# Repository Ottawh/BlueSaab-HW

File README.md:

# BlueSaab-HW
BlueSaab hardware

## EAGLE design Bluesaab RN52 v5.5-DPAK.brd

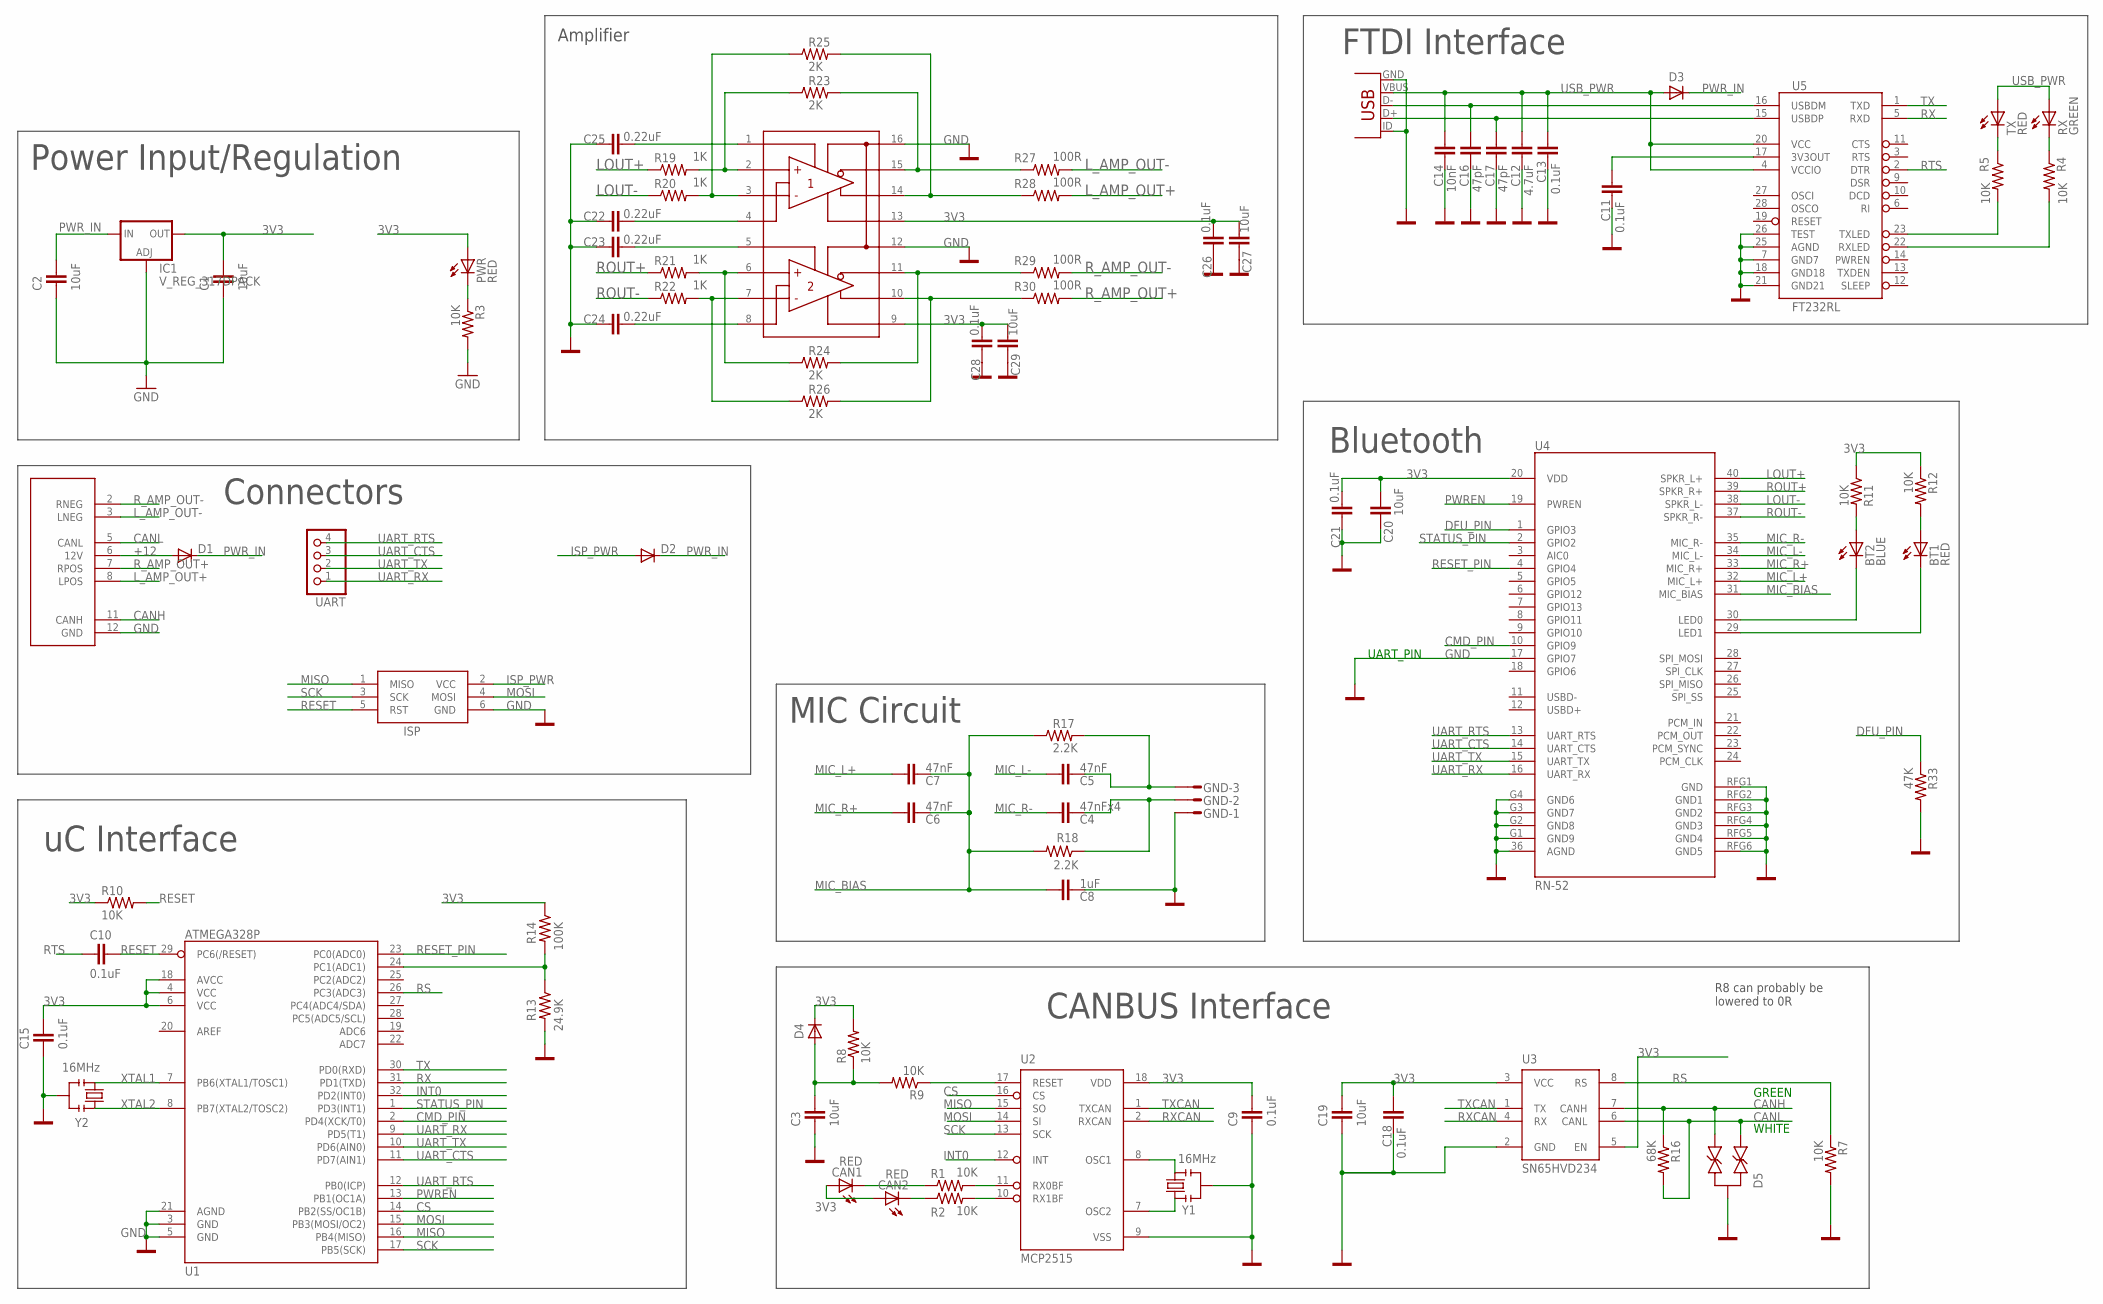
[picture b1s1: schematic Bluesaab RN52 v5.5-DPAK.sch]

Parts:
BT1: RED; CHIPLED_0805
BT2: BLUE; CHIPLED_0805
C1, C2, C3, C19, C20, C27, C29: 10uF; C0805K
C4: 47nFx4; C0805K
C5, C6, C7: 47nF; C0805K
C8: 1uF; C0805K
C9, C10, C11, C13, C15, C18, C21, C26, C28: 0.1uF; C0805K
C12: 4.7uF; C0805K
C14: 10nF; C0805K
C16, C17: 47pF; C0805K
C22, C23, C24, C25: 0.22uF; C0805K
CAN1, CAN2: RED; CHIPLED_0805
CDC_CONNECTOR: 827229-1
D1, D2, D3, D4: DIODE-SCHOTTKY_; SOD123
D5: DIODE-ARRAY; SOT23
GND: S03P
IC1: V_REG_317DPACK; V-REG_DPACK
ISP: AVRISP-6; AVRISP
PWR: RED; CHIPLED_0805
R1, R2, R3, R4, R5, R7, R8, R9, R10, R11, R12: 10K; R0805
R13: 24.9K; R0805
R14: 100K; R0805
R16: 68K; R0805
R17, R18: 2.2K; R0805
R19, R20, R21, R22: 1K; R0805
R23, R24, R25, R26: 2K; R0805
R27, R28, R29, R30: 100R; R0805
R33: 47K; R0805
RX: GREEN; CHIPLED_0805
TX: RED; CHIPLED_0805
U1: ATMEGA328P; TQFP32-08
U2: MCP2515; SO18L
U3: SN65HVD234; SO8
U4: RN-52
U5: FT232RL; SSOP28DB
U7: THS4522; TSSOP-16
UART: PINHD-1X4; 1X04
UPLOAD: USB-MB-H
Y1, Y2: 16MHz; RESONATOR-SMD

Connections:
3V3: C1.2, C9.2, C15.2, C18.1, C19.2, C20.1, C21.2, C26.2, C27.1, C28.2, C29.1, CAN1.A, CAN2.A, D4.C, IC1.4 (OUT), PWR.A, R8.2, R10.1, R11.1, R12.1, R14.1, U1.4 (VCC), U1.6 (VCC), U1.18 (AVCC), U2.18 (VDD), U3.3 (VCC), U3.5 (EN), U4.20 (VDD), U7.9 (9.VS+2), U7.13 (13.VS+1)
3V3OUT: C11.1, U5.17 (3V3OUT)
+12: CDC_CONNECTOR.6 (12V), D1.A
CANH: CDC_CONNECTOR.11 (CANH), D5.2, R16.1, U3.7 (CANH)
CANL: CDC_CONNECTOR.5 (CANL), D5.1, R16.2, U3.6 (CANL)
CMD_PIN: U1.2 (PD4(XCK/T0)), U4.10 (GPIO9)
CS: U1.14 (PB2(SS/OC1B)), U2.16 (CS)
DFU_PIN: R33.1, U4.1 (GPIO3)
GND: C1.1, C2.1, C3.1, C8.1, C9.1, C11.2, C12.1, C13.2, C14.1, C15.1, C16.1, C17.1, C18.2, C19.1, C20.2, C21.1, C22.2, C23.2, C24.2, C25.2, C26.1, C27.2, C28.1, C29.2, CDC_CONNECTOR.12 (GND), D5.3, GND.1, IC1.1 (ADJ), ISP.6 (GND), R3.2, R7.2, R13.2, R33.2, U1.3 (GND), U1.5 (GND), U1.21 (AGND), U2.9 (VSS), U3.2 (GND), U4.17 (GPIO7), U4.36 (AGND), U4.G1 (GND9), U4.G2 (GND8), U4.G3 (GND7), U4.G4 (GND6), U4.RFG1 (GND), U4.RFG2 (GND1), U4.RFG3 (GND2), U4.RFG4 (GND3), U4.RFG5 (GND4), U4.RFG6 (GND5), U5.7 (GND7), U5.18 (GND18), U5.21 (GND21), U5.25 (AGND), U5.26 (TEST), U7.12 (12.VS-), U7.16 (16.VS-), UPLOAD.GND, UPLOAD.ID, Y1.2, Y2.2
INT0: U1.32 (PD2(INT0)), U2.12 (INT)
ISP_PWR: D2.A, ISP.2 (VCC)
LOUT+: R19.1, U4.40 (SPKR_L+)
LOUT-: R20.1, U4.38 (SPKR_L-)
L_AMP_OUT+: CDC_CONNECTOR.8 (LPOS), R28.2
L_AMP_OUT-: CDC_CONNECTOR.3 (LNEG), R27.2
MIC_BIAS: C6.1, C7.1, C8.2, R17.1, R18.2, U4.31 (MIC_BIAS)
MIC_L+: C7.2, U4.32 (MIC_L+)
MIC_L-: C5.1, U4.34 (MIC_L-)
MIC_R+: C6.2, U4.33 (MIC_R+)
MIC_R-: C4.1, U4.35 (MIC_R-)
MISO: ISP.1 (MISO), U1.16 (PB4(MISO)), U2.15 (SO)
MOSI: ISP.4 (MOSI), U1.15 (PB3(MOSI/OC2)), U2.14 (SI)
unnamed: R4.2, U5.22 (RXLED)
unnamed: R19.2, R23.1, U7.2 (2.VIN1+)
unnamed: U2.8 (OSC1), Y1.3
unnamed: U2.7 (OSC2), Y1.1
unnamed: BT1.A, R12.2
unnamed: BT2.A, R11.2
unnamed: R9.1, U2.17 (RESET)
unnamed: R13.1, R14.2, U1.24 (PC1(ADC1))
unnamed: R5.2, U5.23 (TXLED)
unnamed: R20.2, R25.1, U7.3 (3.VIN1-)
unnamed: R4.1, RX.C
unnamed: CAN1.C, R1.1
unnamed: R21.2, R24.1, U7.6 (6.IN2+)
unnamed: R5.1, TX.C
unnamed: CAN2.C, R2.1
unnamed: PWR.C, R3.1
unnamed: R1.2, U2.11 (RX0BF)
unnamed: R22.2, R26.1, U7.7 (7.IN2-)
unnamed: C25.1, U7.1 (1.PD1)
unnamed: C23.1, U7.5 (5.PD2)
unnamed: C22.1, U7.4 (4.OCM1)
unnamed: C4.2, GND.2, R18.1
unnamed: R23.2, R27.1, U7.15 (15.VOUT1-)
unnamed: C5.2, GND.3, R17.2
unnamed: R25.2, R28.1, U7.14 (14.VOUT1+)
unnamed: C24.1, U7.8 (8.VOCM2)
unnamed: BT1.C, U4.29 (LED1)
unnamed: BT2.C, U4.30 (LED0)
unnamed: R2.2, U2.10 (RX1BF)
unnamed: R24.2, R29.1, U7.11 (11.VOUT2-)
unnamed: R26.2, R30.1, U7.10 (10.VOUT2+)
unnamed: C3.2, D4.A, R8.1, R9.2
PWREN: U1.13 (PB1(OC1A)), U4.19 (PWREN)
PWR_IN: C2.2, D1.C, D2.C, D3.C, IC1.3 (IN)
RESET: C10.2, ISP.5 (RST), R10.2, U1.29 (PC6(/RESET))
RESET_PIN: U1.23 (PC0(ADC0)), U4.4 (GPIO4)
ROUT+: R21.1, U4.39 (SPKR_R+)
ROUT-: R22.1, U4.37 (SPKR_R-)
RS: R7.1, U1.26 (PC3(ADC3)), U3.8 (RS)
RTS: C10.1, U5.2 (DTR)
RX: U1.31 (PD1(TXD)), U5.5 (RXD)
RXCAN: U2.2 (RXCAN), U3.4 (RX)
R_AMP_OUT+: CDC_CONNECTOR.7 (RPOS), R30.2
R_AMP_OUT-: CDC_CONNECTOR.2 (RNEG), R29.2
SCK: ISP.3 (SCK), U1.17 (PB5(SCK)), U2.13 (SCK)
STATUS_PIN: U1.1 (PD3(INT1)), U4.2 (GPIO2)
TX: U1.30 (PD0(RXD)), U5.1 (TXD)
TXCAN: U2.1 (TXCAN), U3.1 (TX)
UART_CTS: U1.11 (PD7(AIN1)), U4.14 (UART_CTS), UART.3
UART_RTS: U1.12 (PB0(ICP)), U4.13 (UART_RTS), UART.4
UART_RX: U1.9 (PD5(T1)), U4.16 (UART_RX), UART.1
UART_TX: U1.10 (PD6(AIN0)), U4.15 (UART_TX), UART.2
USBDM: C16.2, U5.16 (USBDM), UPLOAD.D-
USBDP: C17.2, U5.15 (USBDP), UPLOAD.D+
USB_PWR: C12.2, C13.1, C14.2, D3.A, RX.A, TX.A, U5.4 (VCCIO), U5.20 (VCC), UPLOAD.VBUS
XTAL1: U1.7 (PB6(XTAL1/TOSC1)), Y2.1
XTAL2: U1.8 (PB7(XTAL2/TOSC2)), Y2.3

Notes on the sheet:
GREEN
WHITE
CANBUS Interface
Connectors
Power Input/Regulation
Bluetooth
MIC Circuit
uC Interface
UART_PIN
FTDI Interface
R8 can probably be lowered to 0R
Amplifier

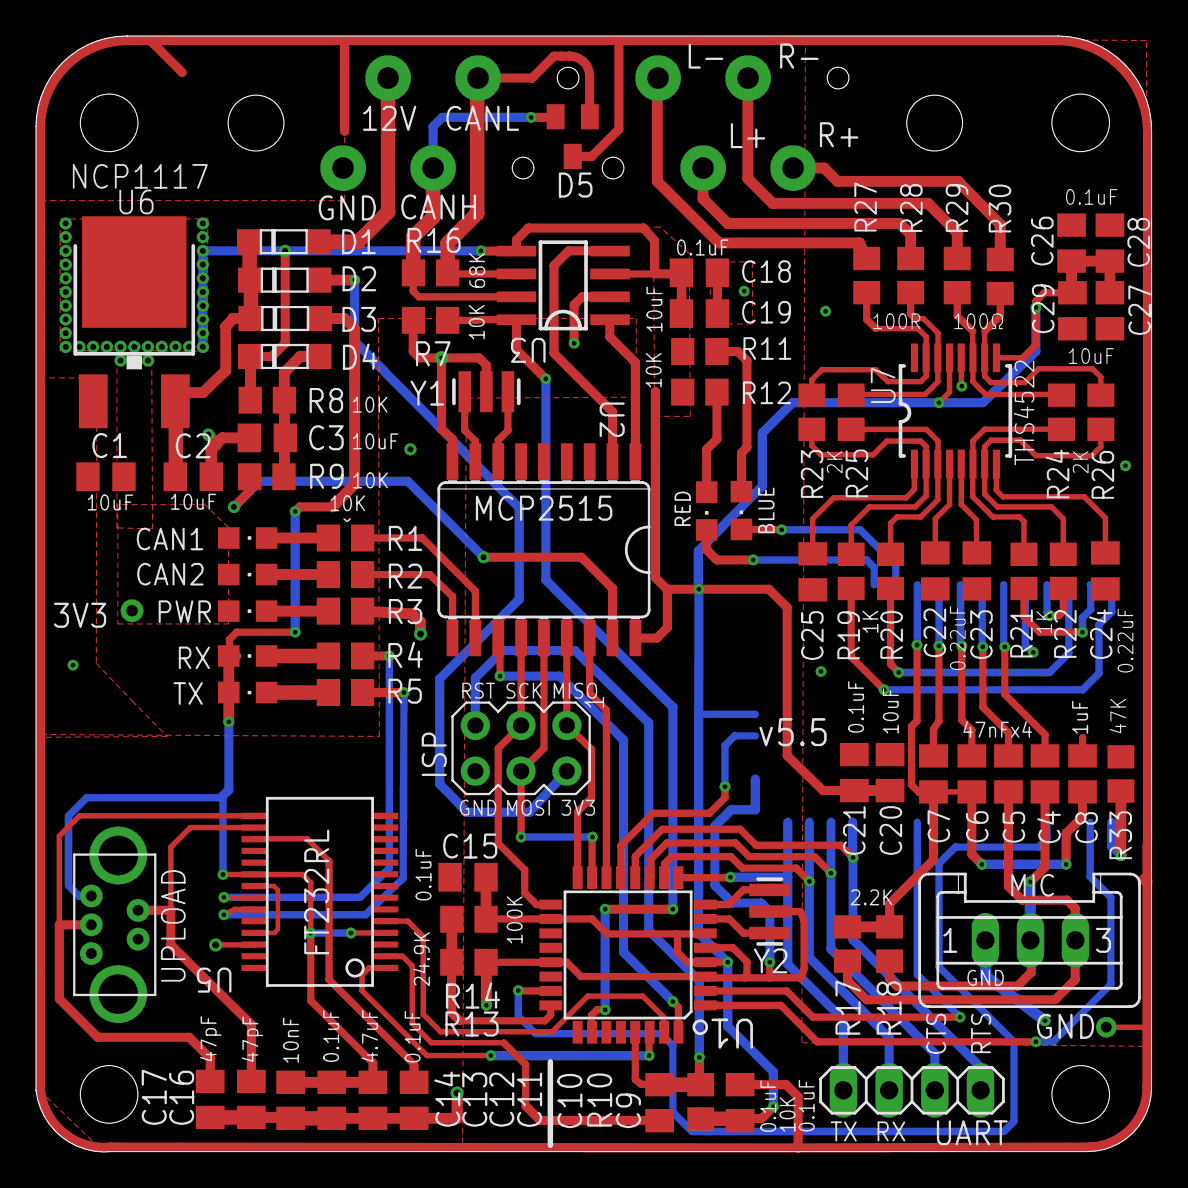
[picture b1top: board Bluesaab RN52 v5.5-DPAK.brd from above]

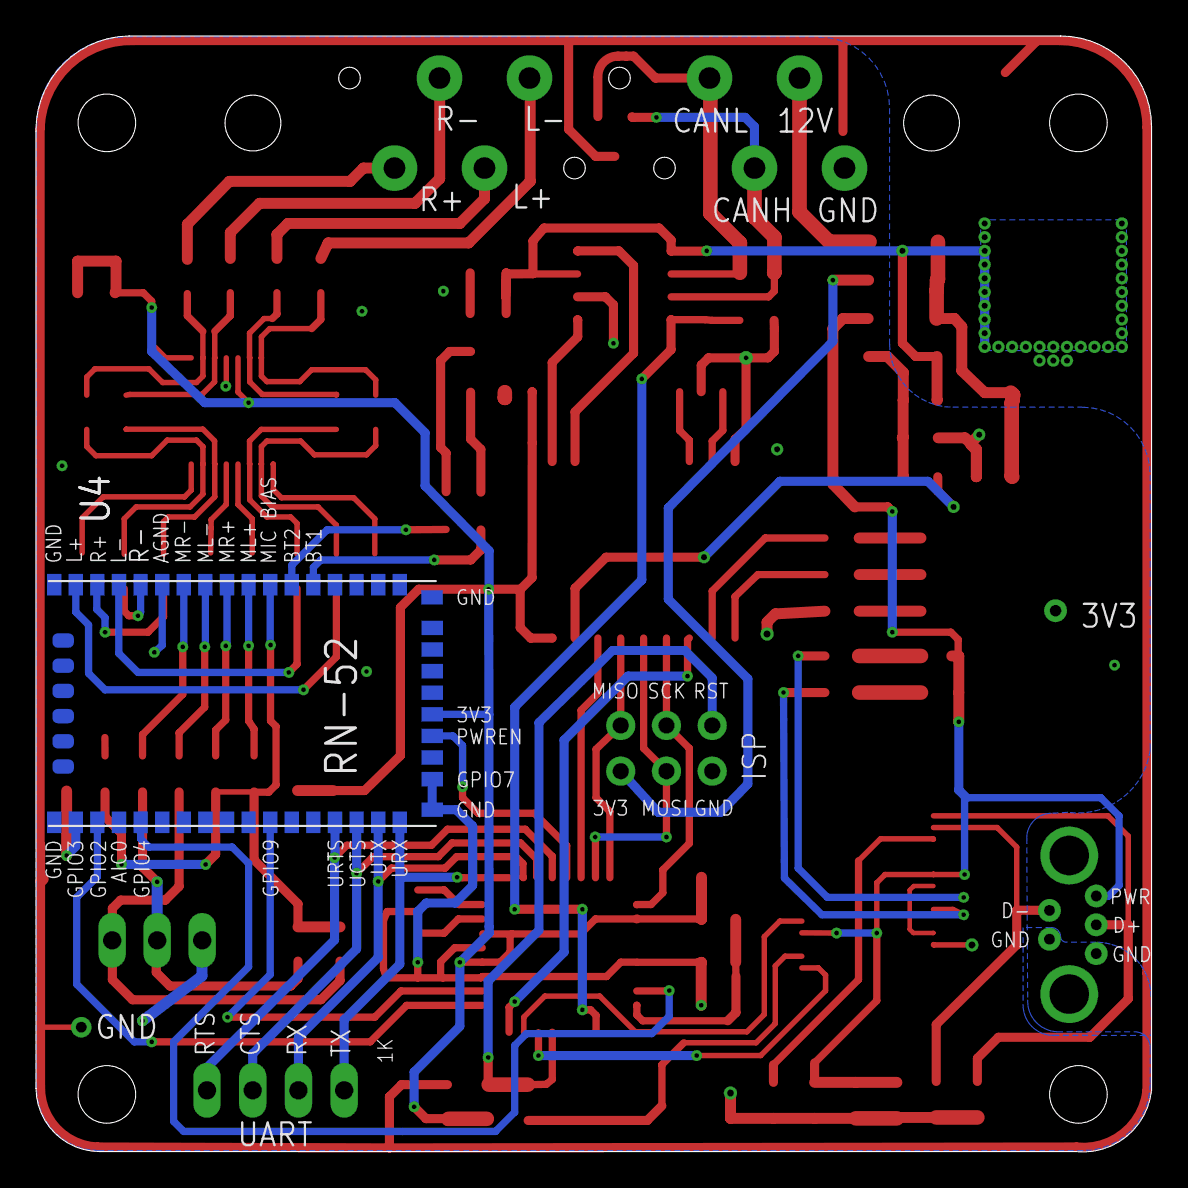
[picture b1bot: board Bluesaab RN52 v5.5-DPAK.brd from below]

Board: 2 copper layers, 62.0 x 62.0 mm, 85 parts (2 on the bottom side), 79 nets.

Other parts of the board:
DRILEGEND: DRILEGEND

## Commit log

2019-06-29 Build 5.5
    Compatible with SW :
    - 4.1
    - 5.1b
2019-06-29 Build 6.1
    Compatible with SW 6.1
2019-06-29 Build 6.1.1
    Compatible with SW 6.1
    This version had fiducials used for pick n place machines

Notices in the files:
parts and their libraries:
SparkFun-DigitalIC: Licensing: CC v3.0 Share-Alike You are welcome to use this library for commercial purposes.
SparkFun-RF: Licensing: Creative Commons ShareAlike 4.0 International - https://creativecommons.org/licenses/by-sa/4.0
